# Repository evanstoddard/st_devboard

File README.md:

# ST Devboard

A simple dev board I created for developing my bootloader (MicroBoot).

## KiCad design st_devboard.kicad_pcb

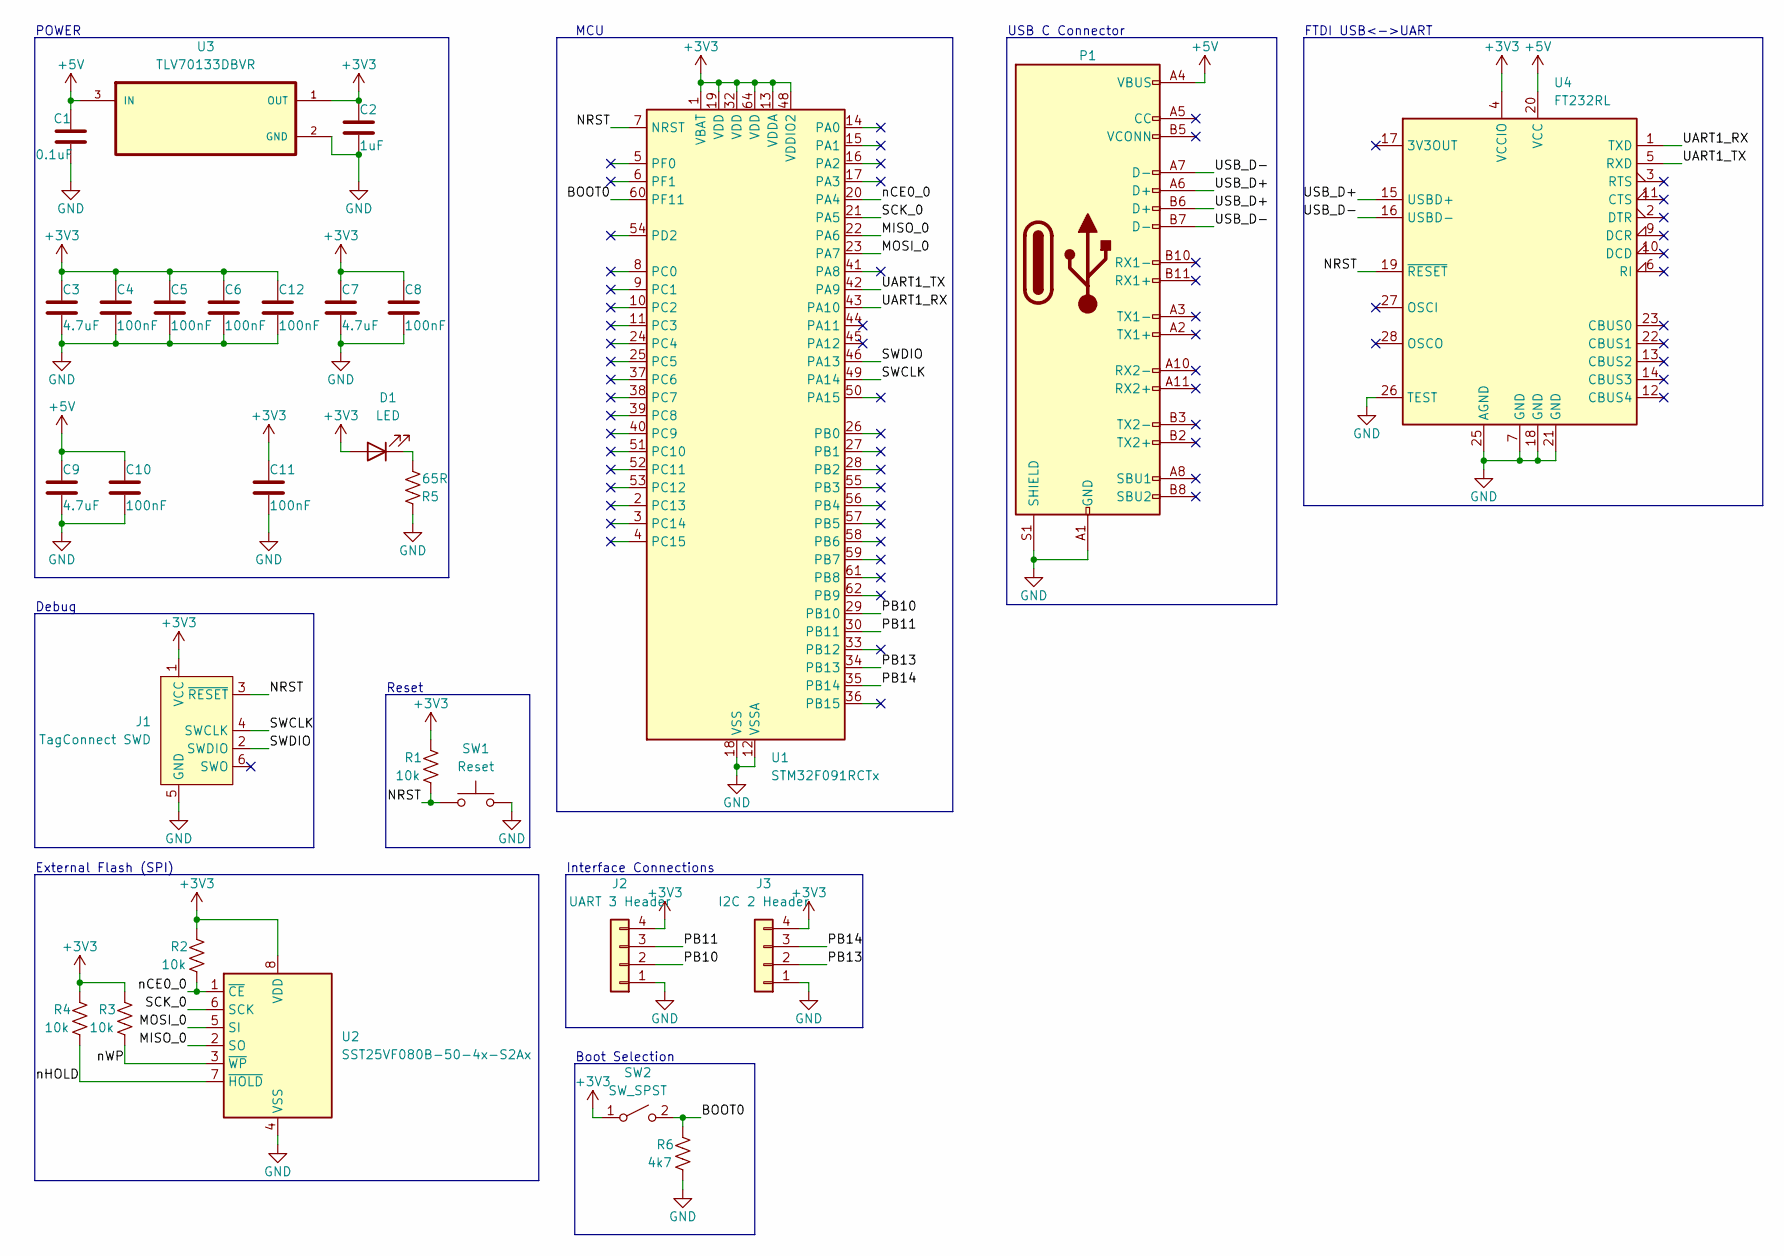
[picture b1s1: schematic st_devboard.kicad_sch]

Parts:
C1: 0.1uF; C_0402_1005Metric_Pad0.74x0.62mm_HandSolder
C2: 1uF; C_0402_1005Metric_Pad0.74x0.62mm_HandSolder
C3, C7, C9: 4.7uF; C_0402_1005Metric_Pad0.74x0.62mm_HandSolder
C4, C5, C6, C8, C10, C11, C12: 100nF; C_0402_1005Metric_Pad0.74x0.62mm_HandSolder
D1: LED; LED_0603_1608Metric
J1: TagConnect SWD; Tag-Connect_TC2030-IDC-FP_2x03_P1.27mm_Vertical
J2: UART 3 Header; PinSocket_1x04_P1.27mm_Vertical
J3: I2C 2 Header; PinSocket_1x04_P1.27mm_Vertical
P1: USB_C_Plug; USB_C_Receptacle_GCT_USB4085
R1, R2, R3, R4: 10k; R_0402_1005Metric_Pad0.72x0.64mm_HandSolder
R5: 65R; R_0402_1005Metric_Pad0.72x0.64mm_HandSolder
R6: 4k7; R_0402_1005Metric_Pad0.72x0.64mm_HandSolder
SW1: Reset; SW_Push_1P1T_NO_CK_KMR2
SW2: SW_SPST; SW_DIP_SPSTx01_Slide_Copal_CHS-01B_W7.62mm_P1.27mm
U1: STM32F091RCTx; LQFP-64_10x10mm_P0.5mm
U2: SST25VF080B-50-4x-S2Ax; SOIC-8_5.275x5.275mm_P1.27mm
U3: TLV70133DBVR; SOT95P280X145-5N
U4: FT232RL; SSOP-28_5.3x10.2mm_P0.65mm

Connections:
+3V3: C2.1, C3.1, C4.1, C5.1, C6.1, C7.1, C8.1, C11.1, C12.1, D1.2 (A), J1.1 (VCC), J2.4, J3.4, R1.1, R2.1, R3.1, R4.1, SW2.1 (A), U1.1 (VBAT), U1.13 (VDDA), U1.19 (VDD), U1.32 (VDD), U1.48 (VDDIO2), U1.64 (VDD), U2.8 (VDD), U3.1 (OUT), U4.4 (VCCIO); also elsewhere on the board
+5V: C1.1, C9.1, C10.1, P1.A4 (VBUS), P1.A9 (VBUS), P1.B4 (VBUS), P1.B9 (VBUS), U3.3 (IN), U4.20 (VCC)
/BOOT0: R6.1, SW2.2 (B), U1.60 (PF11); also elsewhere on the board
/MISO_0: U1.22 (PA6), U2.2 (SO)
/MOSI_0: U1.23 (PA7), U2.5 (SI)
/NRST: J1.3 (~RESET), R1.2, SW1.1, U1.7 (NRST), U4.19 (~RESET)
/PB10: J2.2, U1.29 (PB10)
/PB11: J2.3, U1.30 (PB11)
/PB13: J3.2, U1.34 (PB13)
/PB14: J3.3, U1.35 (PB14)
/SCK_0: U1.21 (PA5), U2.6 (SCK)
/SWCLK: J1.4 (SWCLK), U1.49 (PA14)
/SWDIO: J1.2 (SWDIO), U1.46 (PA13)
/UART1_RX: U1.43 (PA10), U4.1 (TXD)
/UART1_TX: U1.42 (PA9), U4.5 (RXD)
/USB_D+: P1.A6 (D+), P1.B6 (D+), U4.15 (USBD+)
/USB_D-: P1.A7 (D-), P1.B7 (D-), U4.16 (USBD-)
/nCE0_0: R2.2, U1.20 (PA4), U2.1 (~CE)
/nHOLD: R4.2, U2.7 (~HOLD)
/nWP: R3.2, U2.3 (~WP)
GND: C1.2, C2.2, C3.2, C4.2, C5.2, C6.2, C7.2, C8.2, C9.2, C10.2, C11.2, C12.2, J1.5 (GND), J2.1, J3.1, P1.A1 (GND), P1.A12 (GND), P1.B1 (GND), P1.B12 (GND), P1.S1 (SHIELD), R5.1, R6.2, SW1.2, U1.12 (VSSA), U1.18 (VSS), U1.31 (VSS), U1.47 (VSS), U1.63 (VSS), U2.4 (VSS), U3.2 (GND), U4.7 (GND), U4.18 (GND), U4.21 (GND), U4.25 (AGND), U4.26 (TEST)
unnamed: D1.1 (K), R5.2

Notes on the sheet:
Boot Selection
Interface Connections
Reset
MCU
External Flash (SPI)
Debug
FTDI USB<->UART
USB C Connector
POWER

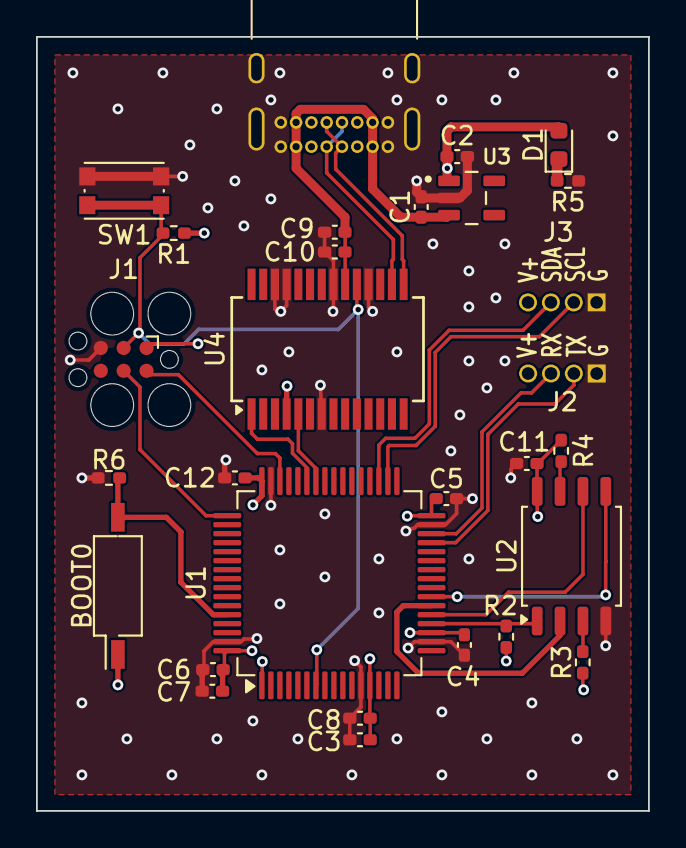
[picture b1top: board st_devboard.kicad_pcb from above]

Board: 4 copper layers, 34.0 x 43.0 mm, 29 parts (0 on the bottom side), 22 nets.

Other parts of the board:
BOOT0: SW_SPST; SW_DIP_SPSTx01_Slide_Copal_CHS-01B_W7.62mm_P1.27mm

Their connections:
+3V3: BOOT0.1 (A); also elsewhere on the board
/BOOT0: BOOT0.2 (B); also elsewhere on the board

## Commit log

2024-04-15 Initial commit.
